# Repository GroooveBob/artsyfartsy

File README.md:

# ARTSY FARTSY
ergo artsey keyboard

Keys and the encoder are working the rest is still a supprise

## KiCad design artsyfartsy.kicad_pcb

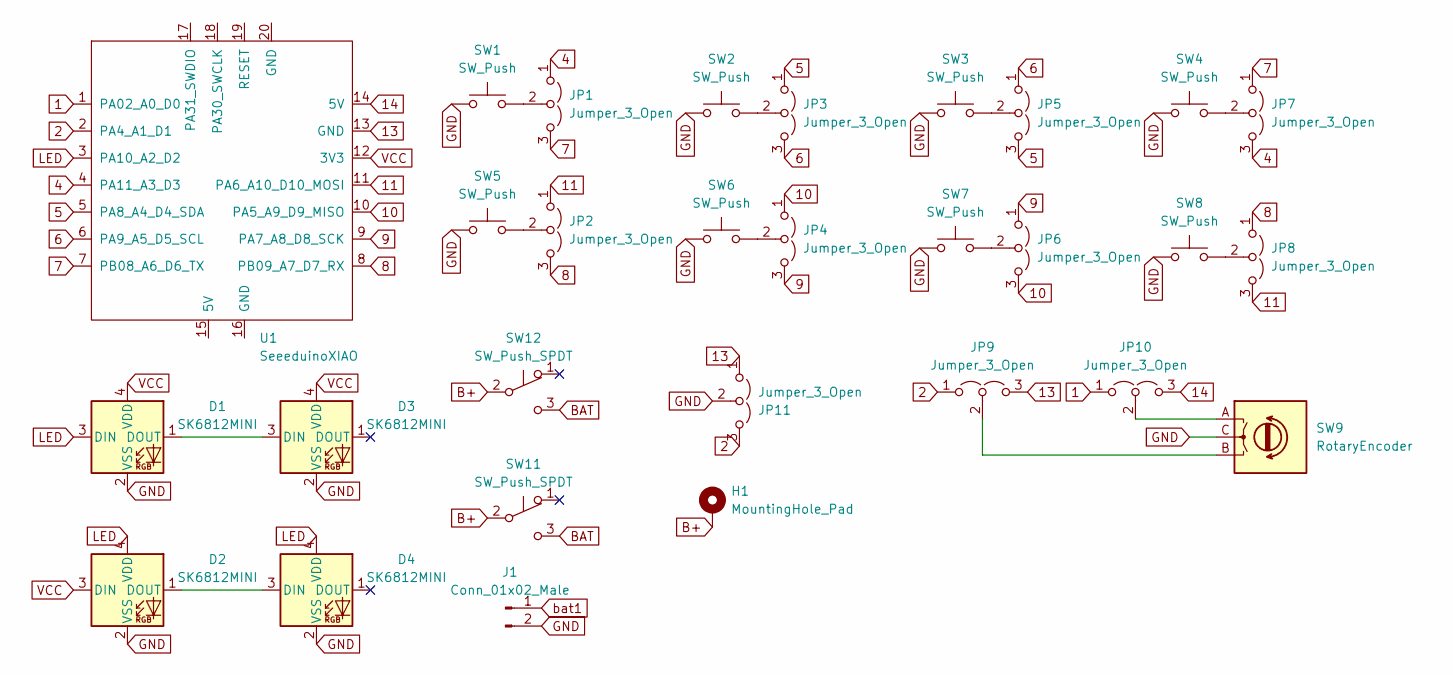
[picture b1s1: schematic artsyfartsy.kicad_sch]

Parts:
D1, D2, D3, D4: SK6812MINI; LED_SK6812MINI_PLCC4_3.5x3.5mm_P1.75mm
H1: MountingHole_Pad; SolderWire-0.15sqmm_1x01_D0.5mm_OD1.5mm
J1: Conn_01x02_Male; JST_EH_S2B-EH_1x02_P2.50mm_Horizontal
JP1, JP2, JP3, JP4, JP5, JP6, JP7, JP8, JP9, JP10, JP11: Jumper_3_Open; SolderJumper-3_P1.3mm_Open_RoundedPad1.0x1.5mm_NumberLabels
SW1, SW2, SW3, SW4, SW5, SW6, SW7, SW8: SW_Push; einmalalles
SW9: RotaryEncoder; RotaryEncoder_EC11
SW11, SW12: SW_Push_SPDT; SW_SPDT_PCM12
U1: SeeeduinoXIAO; xiao-ble-thtbatfach

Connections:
1: JP10.1 (A), U1.1 (PA02_A0_D0)
2: JP9.1 (A), JP11.3 (B), U1.2 (PA4_A1_D1)
4: JP1.1 (A), JP7.3 (B), U1.4 (PA11_A3_D3)
5: JP3.1 (A), JP5.3 (B), U1.5 (PA8_A4_D4_SDA)
6: JP3.3 (B), JP5.1 (A), U1.6 (PA9_A5_D5_SCL)
7: JP1.3 (B), JP7.1 (A), U1.7 (PB08_A6_D6_TX)
8: JP2.3 (B), JP8.1 (A), U1.8 (PB09_A7_D7_RX)
9: JP4.3 (B), JP6.1 (A), U1.9 (PA7_A8_D8_SCK)
10: JP4.1 (A), JP6.3 (B), U1.10 (PA5_A9_D9_MISO)
11: JP2.1 (A), JP8.3 (B), U1.11 (PA6_A10_D10_MOSI)
13: JP9.3 (B), JP11.1 (A), U1.13 (GND)
14: JP10.3 (B), U1.14 (5V)
GND: D1.2 (VSS), D2.2 (VSS), D3.2 (VSS), D4.2 (VSS), J1.2, JP11.2 (C), SW1.1, SW2.1, SW3.1, SW4.1, SW5.1, SW6.1, SW7.1, SW8.1, SW9.C
LED: D1.3 (DIN), D2.4 (VDD), D4.4 (VDD), U1.3 (PA10_A2_D2)
unnamed: D1.1 (DOUT), D3.3 (DIN)
unnamed: D2.1 (DOUT), D4.3 (DIN)
unnamed: JP1.2 (C), SW1.2
unnamed: JP2.2 (C), SW5.2
unnamed: JP3.2 (C), SW2.2
unnamed: JP4.2 (C), SW6.2
unnamed: JP5.2 (C), SW3.2
unnamed: JP6.2 (C), SW7.2
unnamed: JP7.2 (C), SW4.2
unnamed: JP8.2 (C), SW8.2
unnamed: JP9.2 (C), SW9.B
unnamed: JP10.2 (C), SW9.A
VCC: D1.4 (VDD), D2.3 (DIN), D3.4 (VDD), U1.12 (3V3)
so: H1.1, SW11.2 (B), SW12.2 (B)

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
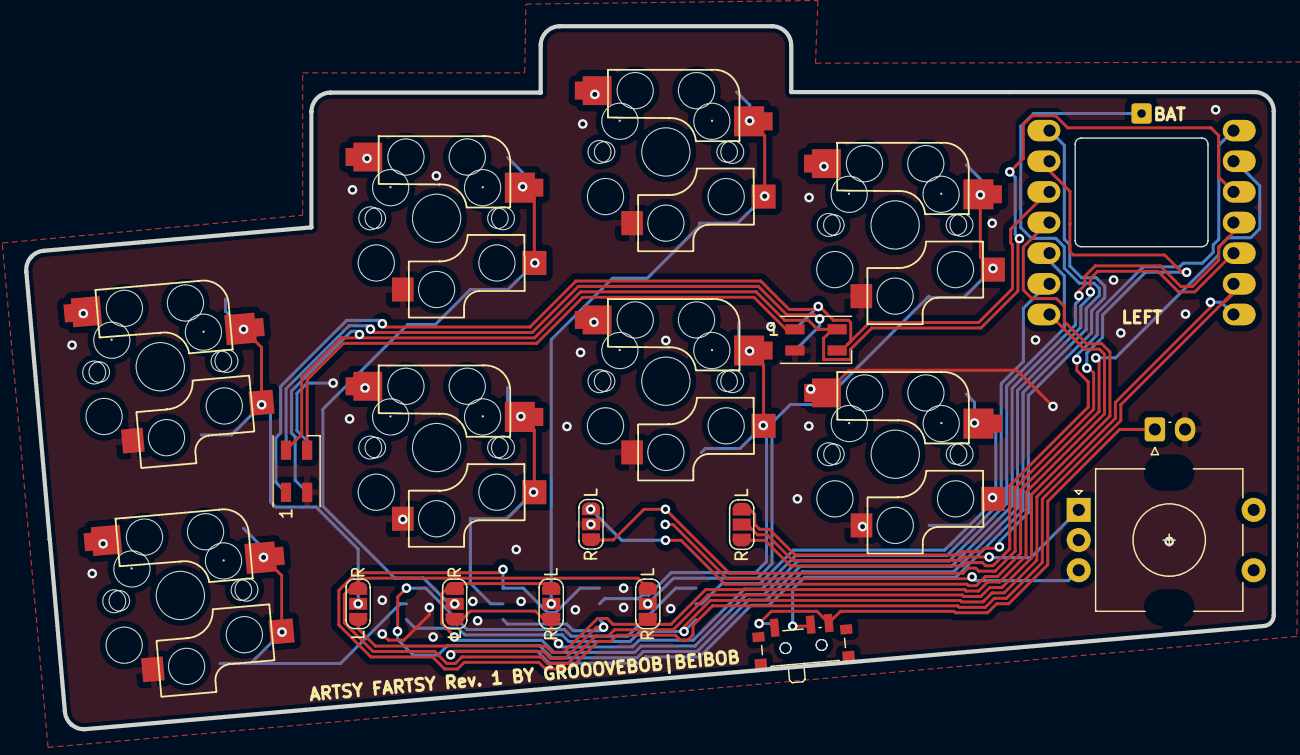
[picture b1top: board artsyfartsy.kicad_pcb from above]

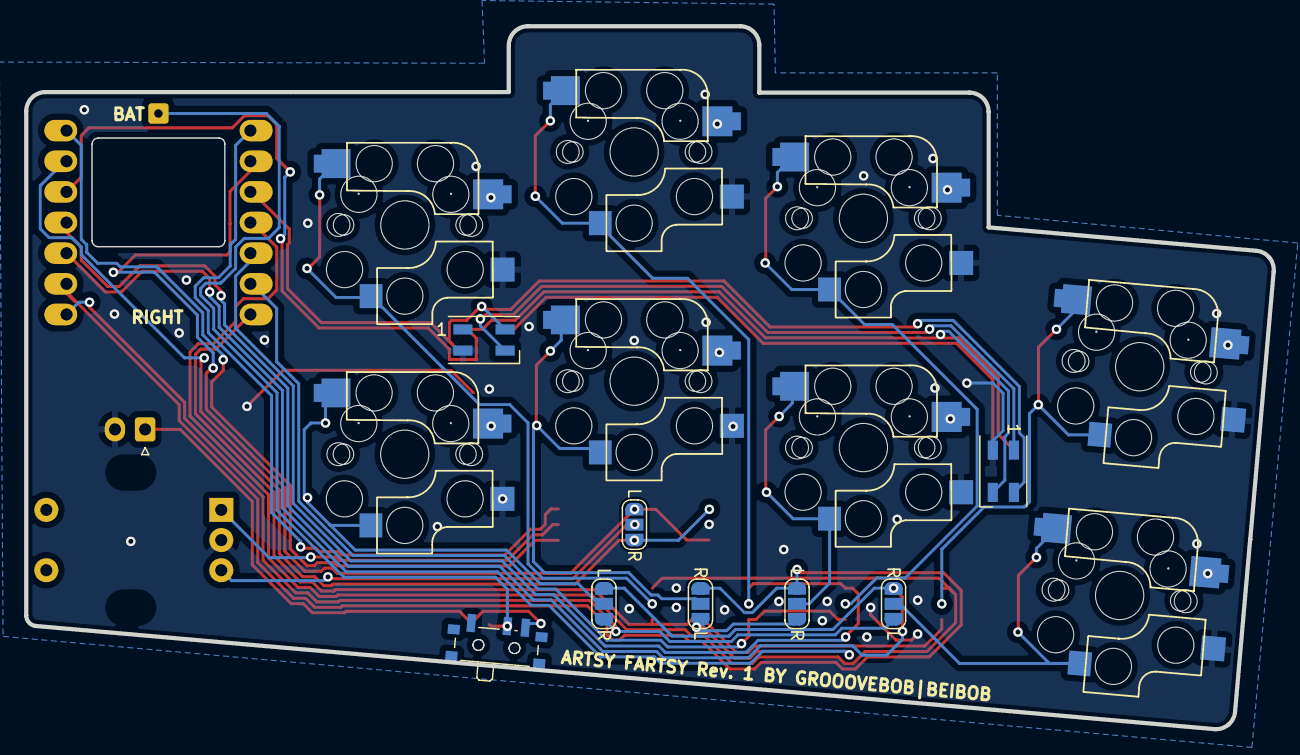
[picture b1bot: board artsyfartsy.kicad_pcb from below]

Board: 2 copper layers, 103.4 x 58.3 mm, 29 parts (8 on the bottom side), 29 nets.

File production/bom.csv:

Designator,Footprint,Quantity,Value,LCSC Part #
SW9,RotaryEncoder_EC11,1,RotaryEncoder,
D1,LED_SK6812MINI_PLCC4_3.5x3.5mm_P1.75mm,1,SK6812MINI,
SW6,einmalalles,1,SW_Push,
SW11,SW_SPDT_PCM12,1,SW_Push_SPDT,
H1,SolderWire-0.15sqmm_1x01_D0.5mm_OD1.5mm,1,MountingHole_Pad,
SW8,einmalalles,1,SW_Push,
JP11,SolderJumper-3_P1.3mm_Open_RoundedPad1.0x1.5mm_NumberLabels,1,Jumper_3_Open,
JP7,SolderJumper-3_P1.3mm_Open_RoundedPad1.0x1.5mm_NumberLabels,1,Jumper_3_Open,
JP10,SolderJumper-3_P1.3mm_Open_RoundedPad1.0x1.5mm_NumberLabels,1,Jumper_3_Open,
JP1,SolderJumper-3_P1.3mm_Open_RoundedPad1.0x1.5mm_NumberLabels,1,Jumper_3_Open,
SW2,einmalalles,1,SW_Push,
JP3,SolderJumper-3_P1.3mm_Open_RoundedPad1.0x1.5mm_NumberLabels,1,Jumper_3_Open,
U1,xiao-ble-thtbatfach,1,SeeeduinoXIAO,
SW4,einmalalles,1,SW_Push,
JP5,SolderJumper-3_P1.3mm_Open_RoundedPad1.0x1.5mm_NumberLabels,1,Jumper_3_Open,
SW5,einmalalles,1,SW_Push,
J1,JST_EH_S2B-EH_1x02_P2.50mm_Horizontal,1,Conn_01x02_Male,
SW3,einmalalles,1,SW_Push,
SW1,einmalalles,1,SW_Push,
SW7,einmalalles,1,SW_Push,
D3,LED_SK6812MINI_PLCC4_3.5x3.5mm_P1.75mm,1,SK6812MINI,
JP2,SolderJumper-3_P1.3mm_Open_RoundedPad1.0x1.5mm_NumberLabels,1,Jumper_3_Open,
JP9,SolderJumper-3_P1.3mm_Open_RoundedPad1.0x1.5mm_NumberLabels,1,Jumper_3_Open,
D4,LED_SK6812MINI_PLCC4_3.5x3.5mm_P1.75mm,1,SK6812MINI,
SW12,SW_SPDT_PCM12,1,SW_Push_SPDT,
JP4,SolderJumper-3_P1.3mm_Open_RoundedPad1.0x1.5mm_NumberLabels,1,Jumper_3_Open,
D2,LED_SK6812MINI_PLCC4_3.5x3.5mm_P1.75mm,1,SK6812MINI,
JP6,SolderJumper-3_P1.3mm_Open_RoundedPad1.0x1.5mm_NumberLabels,1,Jumper_3_Open,
JP8,SolderJumper-3_P1.3mm_Open_RoundedPad1.0x1.5mm_NumberLabels,1,Jumper_3_Open,

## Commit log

2022-09-28 sorry bubble
2022-09-28 encoder
2022-09-29 Create LICENSE
2022-09-30 updated service hole fot battery
2022-09-30 removed sweaty palms
